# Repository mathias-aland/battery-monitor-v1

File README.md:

# battery-monitor-v1
PCBs created with EAGLE 7.7.0  
Gateway FW created with ESP-IDF Eclipse  
Node FW created with Simplicity Studio  
**More info will be added later!**

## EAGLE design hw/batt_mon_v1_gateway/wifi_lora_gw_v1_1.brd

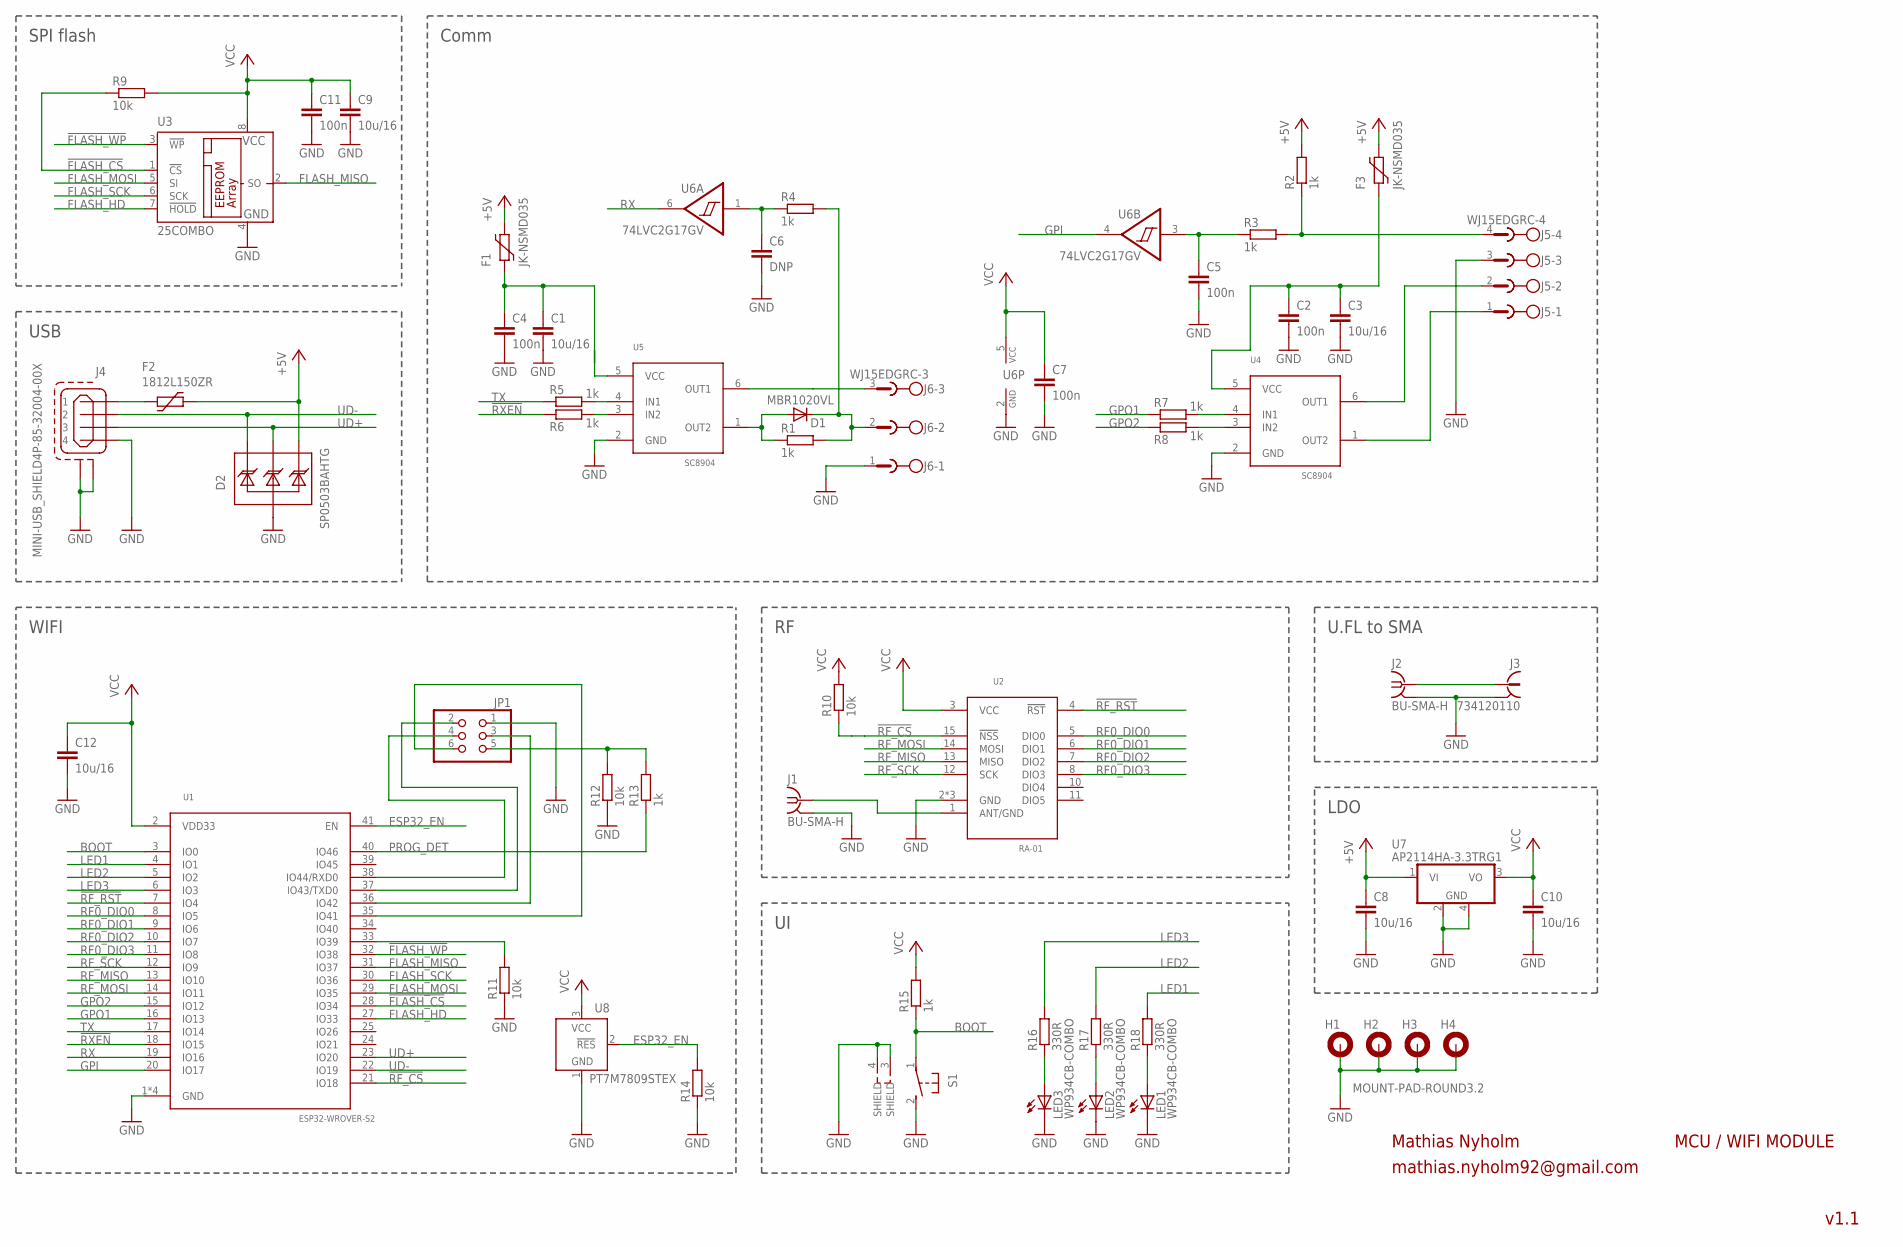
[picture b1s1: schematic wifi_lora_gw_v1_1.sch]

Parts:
C1, C3, C8, C9, C10, C12: 10u/16; C1206
C2, C4, C5, C7, C11: 100n; C0805
C6: DNP; C0805
D1: MBR1020VL; SOD123
D2: SP0503BAHTG; SOT143
F1, F3: JK-NSMD035; 1206L
F2: 1812L150ZR; 1812L
H1, H2, H3, H4: MOUNT-PAD-ROUND3.2; 3,2-PAD
J1, J2: BU-SMA-H
J3: 734120110
J4: MINI-USB_SHIELD4P-85-32004-00X; 85-32004-00X
J5: WJ15EDGRC-4; WJ15EDGRC-3.81-4
J6: WJ15EDGRC-3; WJ15EDGRC-3.81-3
JP1: PINHD-2X3; 2X03
LED1, LED2, LED3: WP934CB-COMBO
R1, R2, R3, R4, R5, R6, R7, R8, R13, R15: 1k; R0805
R9, R10, R11, R12, R14: 10k; R0805
R16, R17, R18: 330R; R0805
S1: 31-XX; B3F-31XX
U1: ESP32-WROVER-S2; ESP32-WROVER-I-S2
U2: RA-01; RA-02
U3: 25COMBO; SO-08M-COMBO
U4, U5: SC8904; SOT23-6L
U6: 74LVC2G17GV; SOT23-6L
U7: AP2114HA-3.3TRG1; SOT223
U8: PT7M7809STEX; SOT23B-3

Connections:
!FLASH_CS: R9.1, U1.28 (IO34), U3.1 (!CS)
!FLASH_WP: U1.32 (IO38), U3.3 (!WP)
!RF_CS: R10.1, U1.21 (IO18), U2.15 (!NSS!)
!RF_RST: U1.7 (IO4), U2.4 (!RST!)
!RXEN: R6.1, U1.18 (IO15)
+5V: C8.1, D2.4 (C3), F1.P$2 (2), F2.P$2 (2), F3.P$2 (2), R2.2, U7.1 (VI)
BOOT: R15.1, S1.1, U1.3 (IO0)
ESP32_EN: R14.2, U1.41 (EN), U8.2 (!RES)
FLASH_HD: U1.27 (IO33), U3.7 (!HOLD)
FLASH_MISO: U1.31 (IO37), U3.2 (SO)
FLASH_MOSI: U1.29 (IO35), U3.5 (SI)
FLASH_SCK: U1.30 (IO36), U3.6 (SCK)
GND: C1.2, C2.2, C3.2, C4.2, C5.2, C6.2, C7.2, C8.2, C9.2, C10.2, C11.2, C12.2, D2.1 (A), H1.B3,2, H2.B3,2, H3.B3,2, H4.B3,2, J1.2 (GND), J1.3 (GND), J1.4 (GND), J1.5 (GND), J2.2 (GND), J2.3 (GND), J2.4 (GND), J2.5 (GND), J3.S@1 (2), J3.S@2 (2), J3.S@3 (2), J4.4, J4.M1 (S1), J4.M2 (S2), J5.3, J6.1, JP1.1, LED1.K (C), LED1.K1 (C), LED2.K (C), LED2.K1 (C), LED3.K (C), LED3.K1 (C), R11.1, R12.1, R14.1, S1.2 (S), S1.3 (SHIELD), S1.4 (SHIELD), U1.1 (GND), U1.26 (GND), U1.42 (GND), U1.43 (GND), U2.2 (GND), U2.9 (GND), U2.16 (GND), U3.4 (GND), U4.2 (GND), U5.2 (GND), U6.2 (GND), U7.2 (GND), U7.4 (GND), U8.1 (GND)
GPI: U1.20 (IO17), U6.4 (O)
GPO1: R7.1, U1.16 (IO13)
GPO2: R8.1, U1.15 (IO12)
LED1: R18.2, U1.4 (IO1)
LED2: R17.2, U1.5 (IO2)
LED3: R16.2, U1.6 (IO3)
unnamed: LED1.A, LED1.A1 (A), R18.1
unnamed: JP1.5, R12.2, R13.2
unnamed: D1.A, R1.1, U5.1 (OUT2)
unnamed: R5.2, U5.4 (IN1)
unnamed: F2.P$1 (1), J4.1
unnamed: JP1.4, U1.38 (IO44/RXD0)
unnamed: JP1.3, U1.36 (IO42)
unnamed: R11.2, U1.33 (IO39)
unnamed: JP1.6, U1.35 (IO41)
unnamed: JP1.2, U1.37 (IO43/TXD0)
unnamed: C1.1, C4.1, F1.P$1 (1), U5.5 (VCC)
unnamed: D1.C, J6.2, R1.2, R4.2
unnamed: J5.4, R2.1, R3.2
unnamed: J5.2, U4.6 (OUT1)
unnamed: J5.1, U4.1 (OUT2)
unnamed: C6.1, R4.1, U6.1 (I)
unnamed: R6.2, U5.3 (IN2)
unnamed: C5.1, R3.1, U6.3 (I)
unnamed: R7.2, U4.4 (IN1)
unnamed: LED3.A, LED3.A1 (A), R16.1
unnamed: LED2.A, LED2.A1 (A), R17.1
unnamed: J1.1, U2.1 (ANT/GND)
unnamed: J2.1, J3.1
unnamed: J6.3, U5.6 (OUT1)
unnamed: C2.1, C3.1, F3.P$1 (1), U4.5 (VCC)
unnamed: R8.2, U4.3 (IN2)
PROG_DET: R13.1, U1.40 (IO46)
RF0_DIO0: U1.8 (IO5), U2.5 (DIO0)
RF0_DIO1: U1.9 (IO6), U2.6 (DIO1)
RF0_DIO2: U1.10 (IO7), U2.7 (DIO2)
RF0_DIO3: U1.11 (IO8), U2.8 (DIO3)
RF_MISO: U1.13 (IO10), U2.13 (MISO)
RF_MOSI: U1.14 (IO11), U2.14 (MOSI)
RF_SCK: U1.12 (IO9), U2.12 (SCK)
RX: U1.19 (IO16), U6.6 (O)
TX: R5.1, U1.17 (IO14)
UD+: D2.3 (C2), J4.3, U1.23 (IO20)
UD-: D2.2 (C1), J4.2, U1.22 (IO19)
VCC: C7.1, C9.1, C10.1, C11.1, C12.1, R9.2, R10.2, R15.2, U1.2 (VDD33), U2.3 (VCC), U3.8 (VCC), U6.5 (VCC), U7.3 (VO), U8.3 (VCC)

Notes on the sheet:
MCU / WIFI MODULE
v1.1
Mathias Nyholm
mathias.nyholm92@gmail.com
SPI flash
USB
Comm
WIFI
U.FL to SMA
LDO

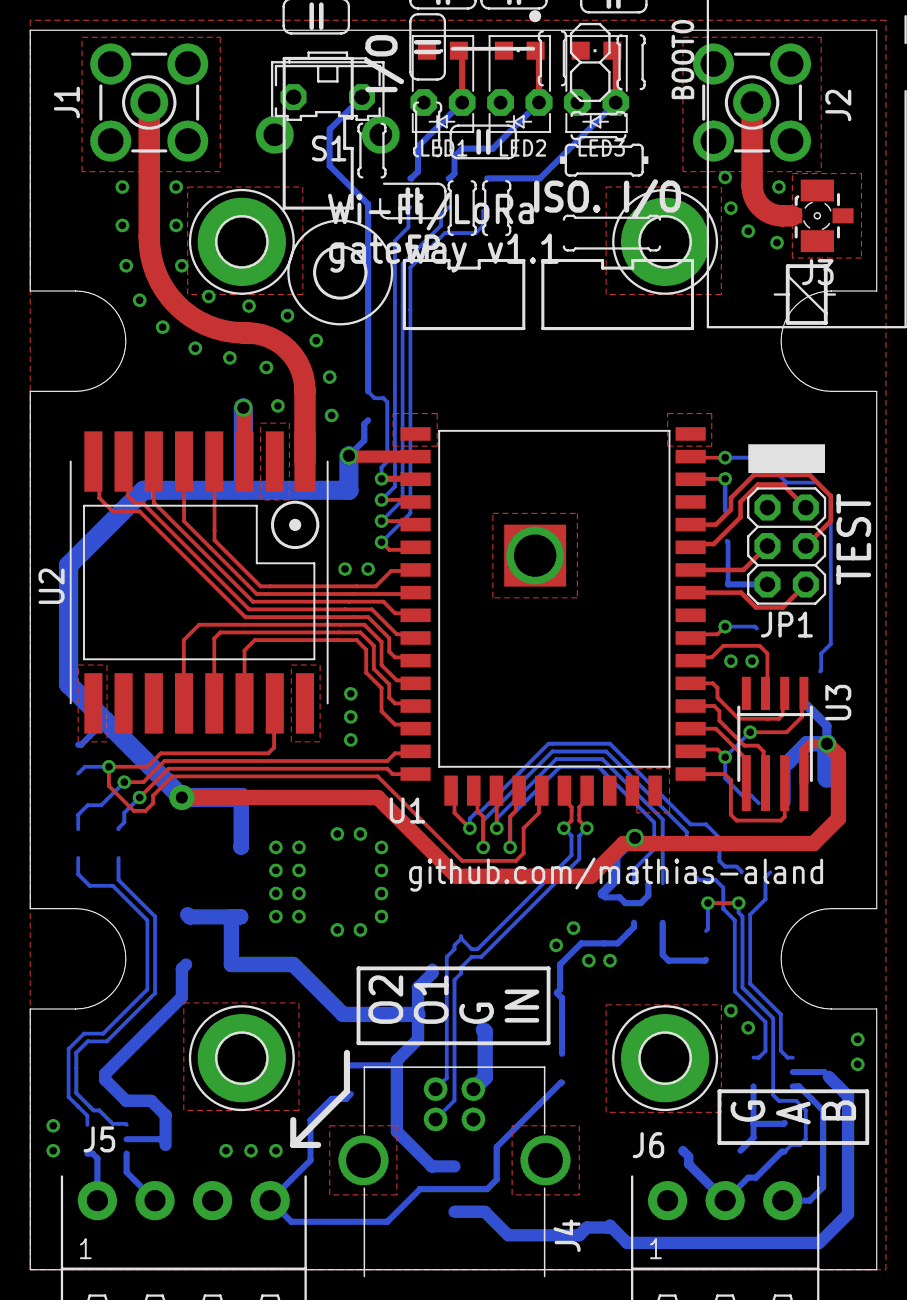
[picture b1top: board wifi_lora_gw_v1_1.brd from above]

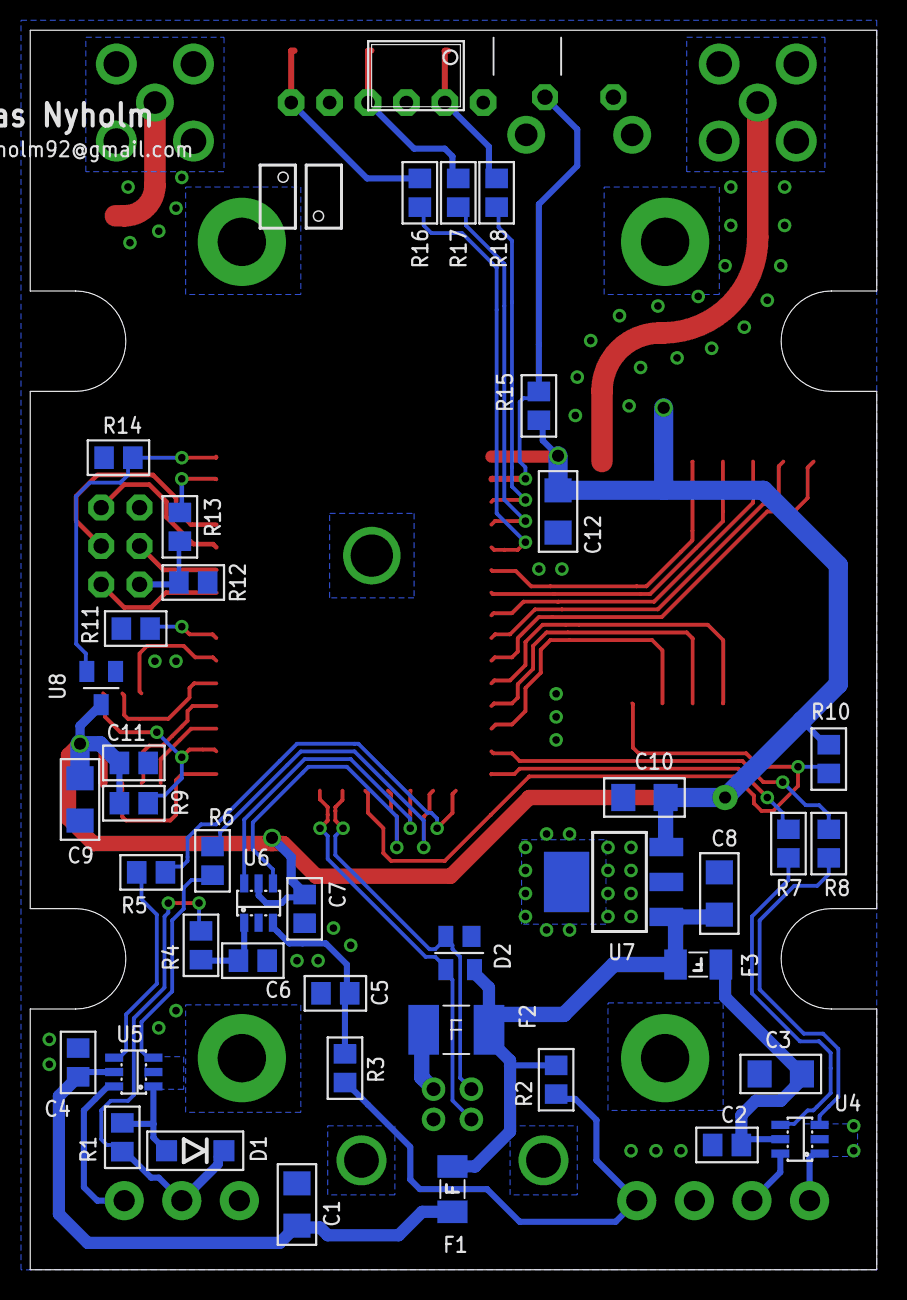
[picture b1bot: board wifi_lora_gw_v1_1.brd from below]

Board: 2 copper layers, 56.0 x 82.0 mm, 58 parts (40 on the bottom side), 58 nets.

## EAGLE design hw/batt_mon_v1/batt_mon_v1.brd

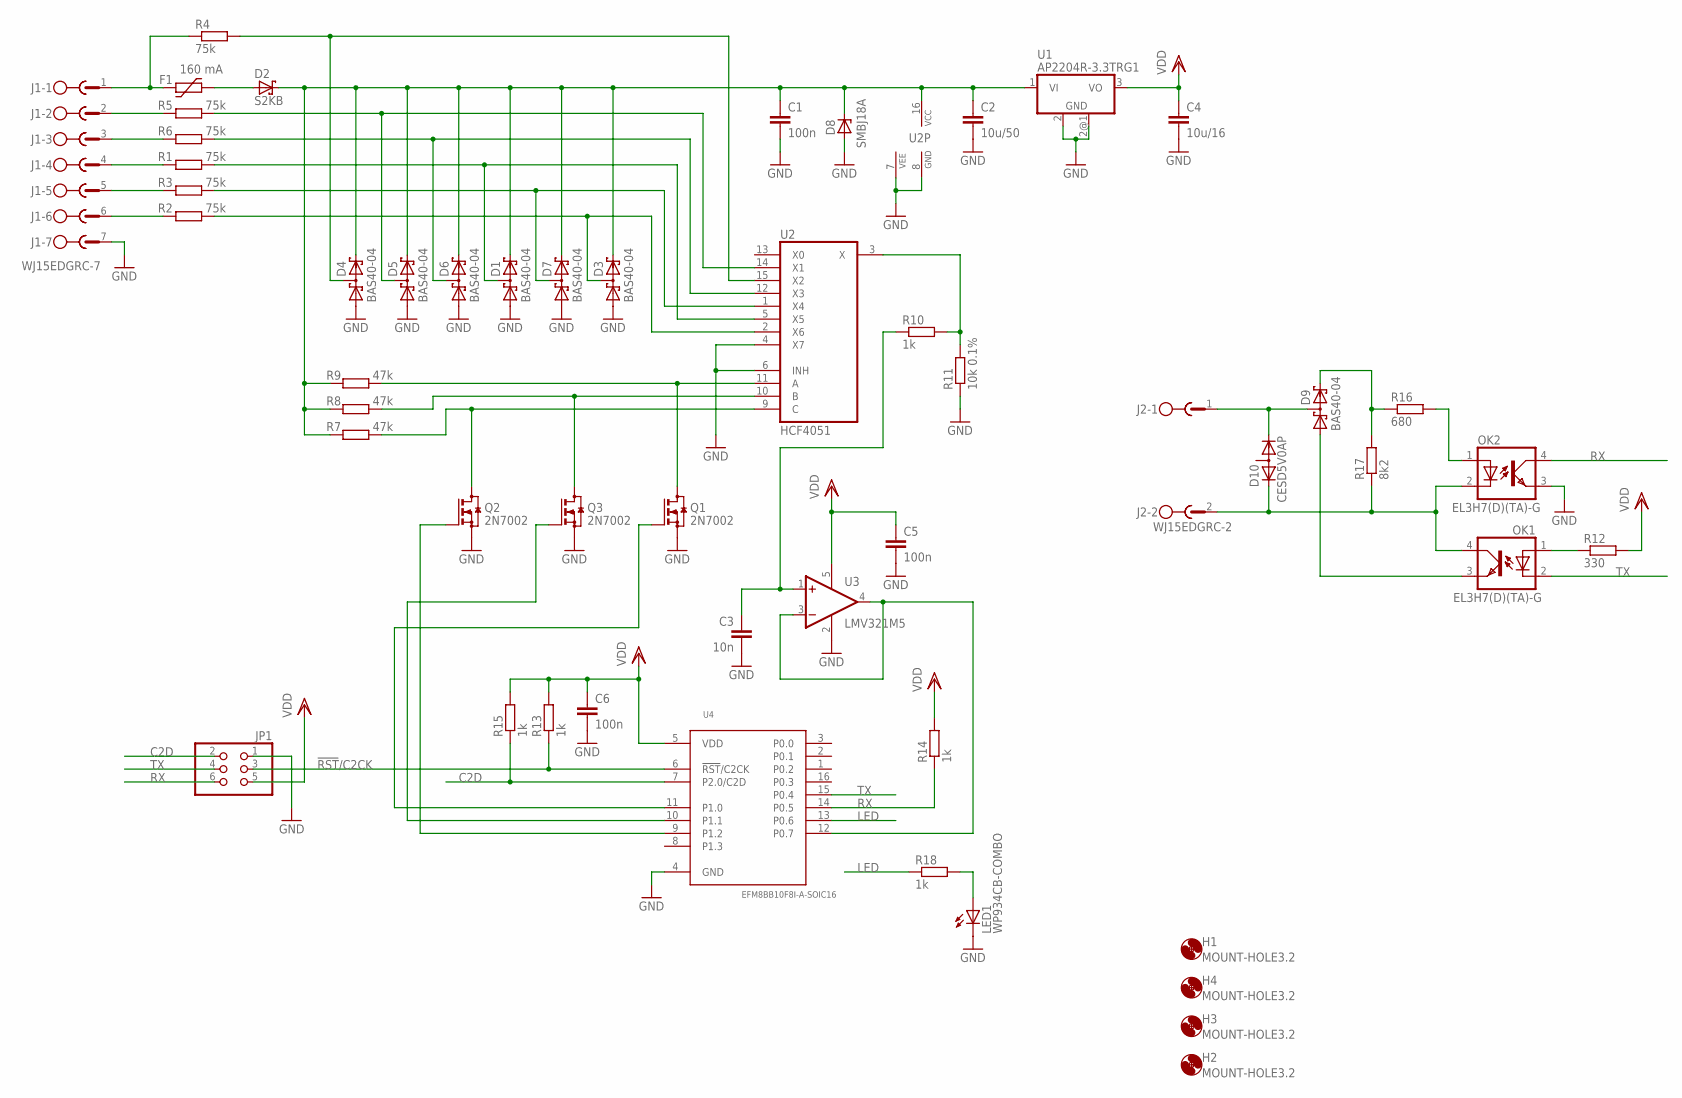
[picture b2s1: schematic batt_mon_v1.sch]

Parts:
C1, C5, C6: 100n; C0805
C2: 10u/50; C1206
C3: 10n; C0805
C4: 10u/16; C1206
D1, D3, D4, D5, D6, D7, D9: BAS40-04; SOT23
D2: S2KB; SMB
D8: SMBJ18A; SMB
D10: CESD5V0AP; SOT23
F1: 160 mA; 1206L
H1, H2, H3, H4: MOUNT-HOLE3.2; 3,2
J1: WJ15EDGRC-7; WJ15EDGRC-3.81-7
J2: WJ15EDGRC-2; WJ15EDGRC-3.81-2
JP1: PINHD-2X3; 2X03
LED1: WP934CB-COMBO
OK1, OK2: EL3H7(D)(TA)-G; MINI-FLAT-4
Q1, Q2, Q3: 2N7002; SOT23
R1, R2, R3, R4, R5, R6: 75k; R1206
R7, R8, R9: 47k; R0805
R10, R13, R14, R15, R18: 1k; R0805
R11: 10k 0.1%; R0805
R12: 330; R0805
R16: 680; R0805
R17: 8k2; R0805
U1: AP2204R-3.3TRG1; SOT89; MOUSER 579-MCP1755ST1802EDB
U2: HCF4051; SO16
U3: LMV321M5; SOT23-5
U4: EFM8BB10F8I-A-SOIC16; SO16

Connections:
!RST!/C2CK: JP1.3, R13.1, U4.6 (!RST!/C2CK)
C2D: JP1.2, R15.1, U4.7 (P2.0/C2D)
GND: C1.2, C2.2, C3.2, C4.2, C5.2, C6.2, D1.1 (A1), D3.1 (A1), D4.1 (A1), D5.1 (A1), D6.1 (A1), D7.1 (A1), D8.A, J1.7, JP1.1, LED1.K (C), LED1.K1 (C), OK2.3 (EMIT), Q1.2 (S), Q2.2 (S), Q3.2 (S), R11.1, U1.2 (GND), U1.2@1 (GND), U2.4 (X7), U2.6 (INH), U2.7 (VEE), U2.8 (GND), U3.2 (V-), U4.4 (GND)
LED: R18.1, U4.13 (P0.6)
unnamed: R10.2, R11.2, U2.3 (X)
unnamed: Q1.3 (D), R9.2, U2.11 (A)
unnamed: Q3.3 (D), R8.2, U2.10 (B)
unnamed: Q2.3 (D), R7.2, U2.9 (C)
unnamed: D1.3 (C1A2), R1.2, U2.5 (X5)
unnamed: F1.P$1 (1), J1.1, R4.1
unnamed: D4.3 (C1A2), R4.2, U2.15 (X2)
unnamed: J1.2, R5.1
unnamed: D5.3 (C1A2), R5.2, U2.14 (X1)
unnamed: D6.3 (C1A2), R6.2, U2.12 (X3)
unnamed: J1.3, R6.1
unnamed: C3.1, R10.1, U3.1 (+IN)
unnamed: D2.A, F1.P$2 (2)
unnamed: J1.4, R1.1
unnamed: Q2.1 (G), U4.9 (P1.2)
unnamed: Q3.1 (G), U4.10 (P1.1)
unnamed: Q1.1 (G), U4.11 (P1.0)
unnamed: C1.1, C2.1, D1.2 (C2), D2.C, D3.2 (C2), D4.2 (C2), D5.2 (C2), D6.2 (C2), D7.2 (C2), D8.C, R7.1, R8.1, R9.1, U1.1 (VI), U2.16 (VCC)
unnamed: J1.6, R2.1
unnamed: J1.5, R3.1
unnamed: OK2.1 (A), R16.2
unnamed: D9.1 (A1), OK1.3 (EMIT)
unnamed: OK1.1 (A), R12.1
unnamed: D9.3 (C1A2), D10.1 (K1), J2.1
unnamed: U3.3 (-IN), U3.4 (OUT), U4.12 (P0.7)
unnamed: D3.3 (C1A2), R2.2, U2.2 (X6)
unnamed: D9.2 (C2), R16.1, R17.2
unnamed: LED1.A, LED1.A1 (A), R18.2
unnamed: D7.3 (C1A2), R3.2, U2.1 (X4)
R-: D10.2 (K2), J2.2, OK1.4 (COL), OK2.2 (C), R17.1
RX: JP1.6, OK2.4 (COL), R14.1, U4.14 (P0.5)
TX: JP1.4, OK1.2 (C), U4.15 (P0.4)
VDD: C4.1, C5.1, C6.1, JP1.5, R12.2, R13.2, R14.2, R15.2, U1.3 (VO), U3.5 (V+), U4.5 (VDD)

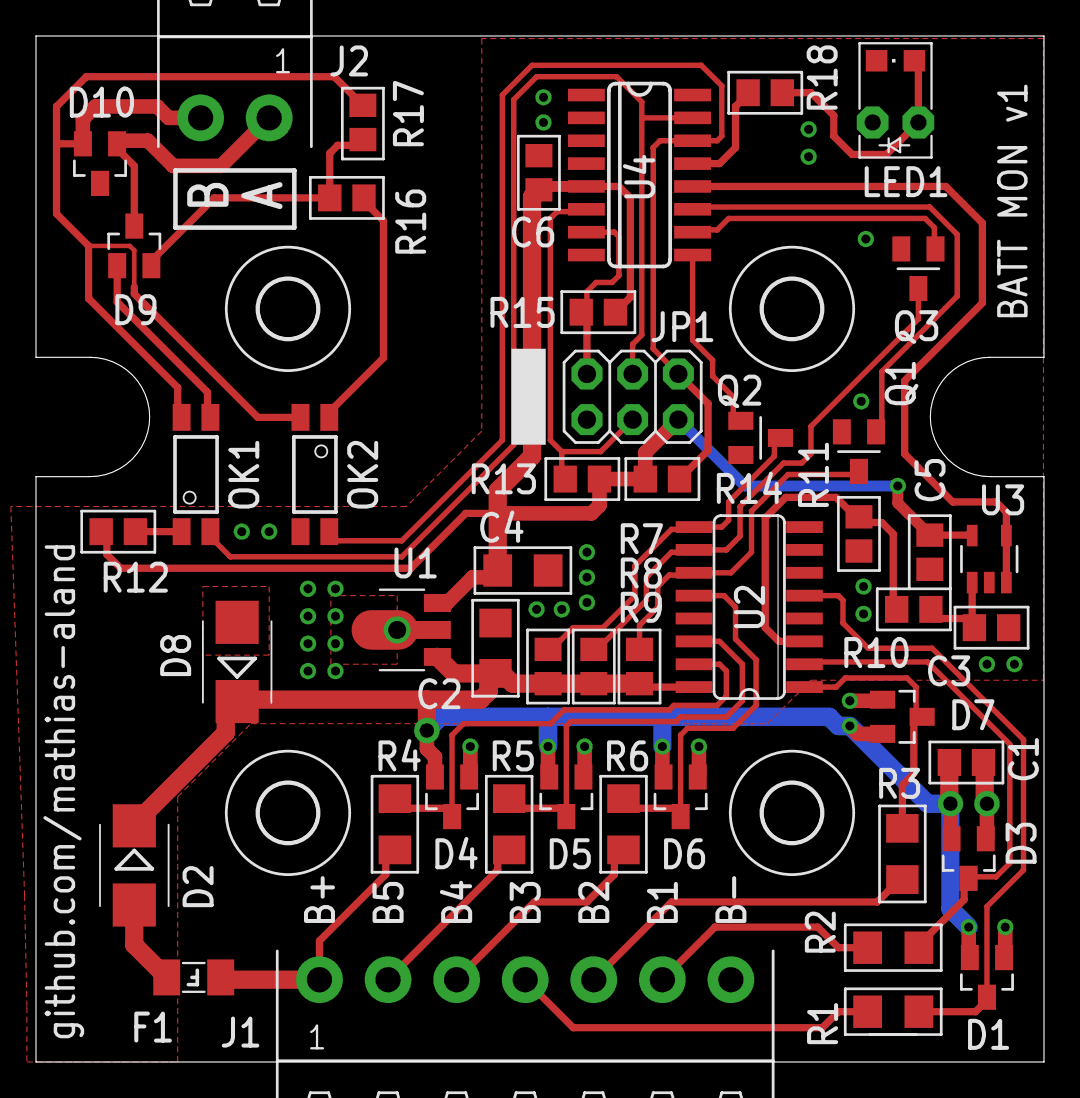
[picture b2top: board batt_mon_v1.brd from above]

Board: 2 copper layers, 56.0 x 57.0 mm, 52 parts (0 on the bottom side), 37 nets.

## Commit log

2021-09-06 Basic functionality working
    Fetching ADC values via UART working, so far only tested with USB TTL adapter and PC software. Sleep mode implemented to save power.
2021-09-08 Add calibration and addressing functionality
    Also change to 2400 baud and some minor fixes
2021-09-08 Create LICENSE
2021-09-16 Add bootloader
2021-09-16 Fix tabs in boot_startup.asm
2021-12-16 Use 0x00 as failsafe address in bootloader
2021-12-16 Fix bugs and add functionality in main FW
2021-12-16 Add Wi-Fi GW code
2021-12-17 Gateway FW improvements
    - Cleanup code
    - Improve network events handling
    - Add RSSI indicator
2021-12-18 Add schematic and layout for nodes
2021-12-18 Add missing paste layers for node PCB
2021-12-18 Add schematic and layout for gateway
